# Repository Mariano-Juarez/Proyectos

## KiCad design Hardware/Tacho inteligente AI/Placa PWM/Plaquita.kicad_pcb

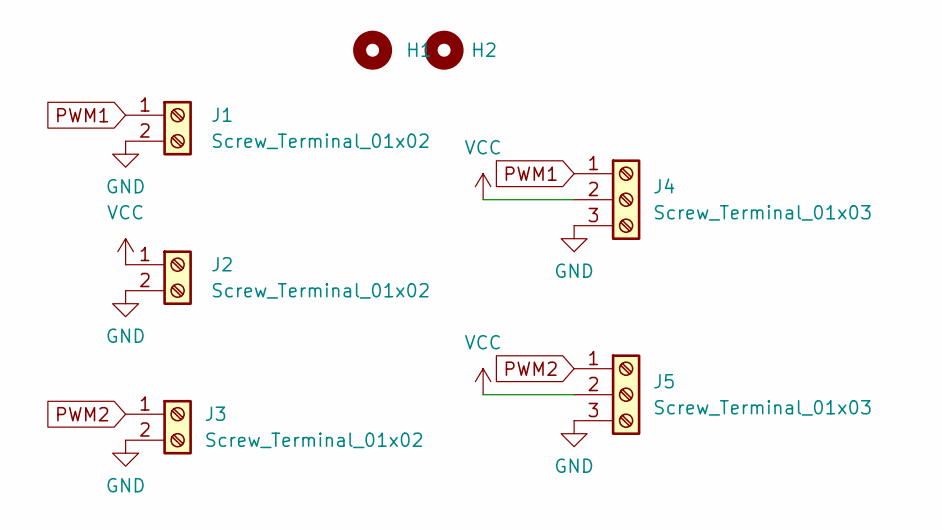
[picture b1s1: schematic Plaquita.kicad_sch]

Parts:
H1, H2: Mounting_Hole; MountingHole_3.5mm
J1, J2, J3: Screw_Terminal_01x02; TerminalBlock_Altech_AK300-2_P5.00mm
J4, J5: Screw_Terminal_01x03; TerminalBlock_Altech_AK300-3_P5.00mm

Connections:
GND: J1.2, J2.2, J3.2, J4.3, J5.3
PWM1: J1.1, J4.1
PWM2: J3.1, J5.1
VCC: J2.1, J4.2, J5.2

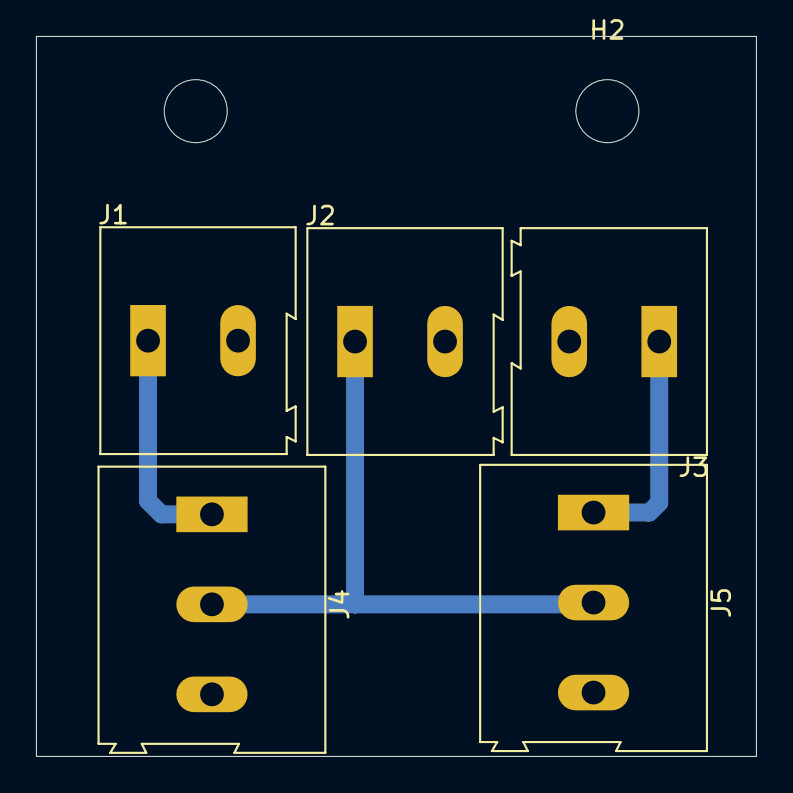
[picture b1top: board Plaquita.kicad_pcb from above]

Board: 2 copper layers, 40.0 x 40.0 mm, 7 parts (0 on the bottom side), 4 nets.

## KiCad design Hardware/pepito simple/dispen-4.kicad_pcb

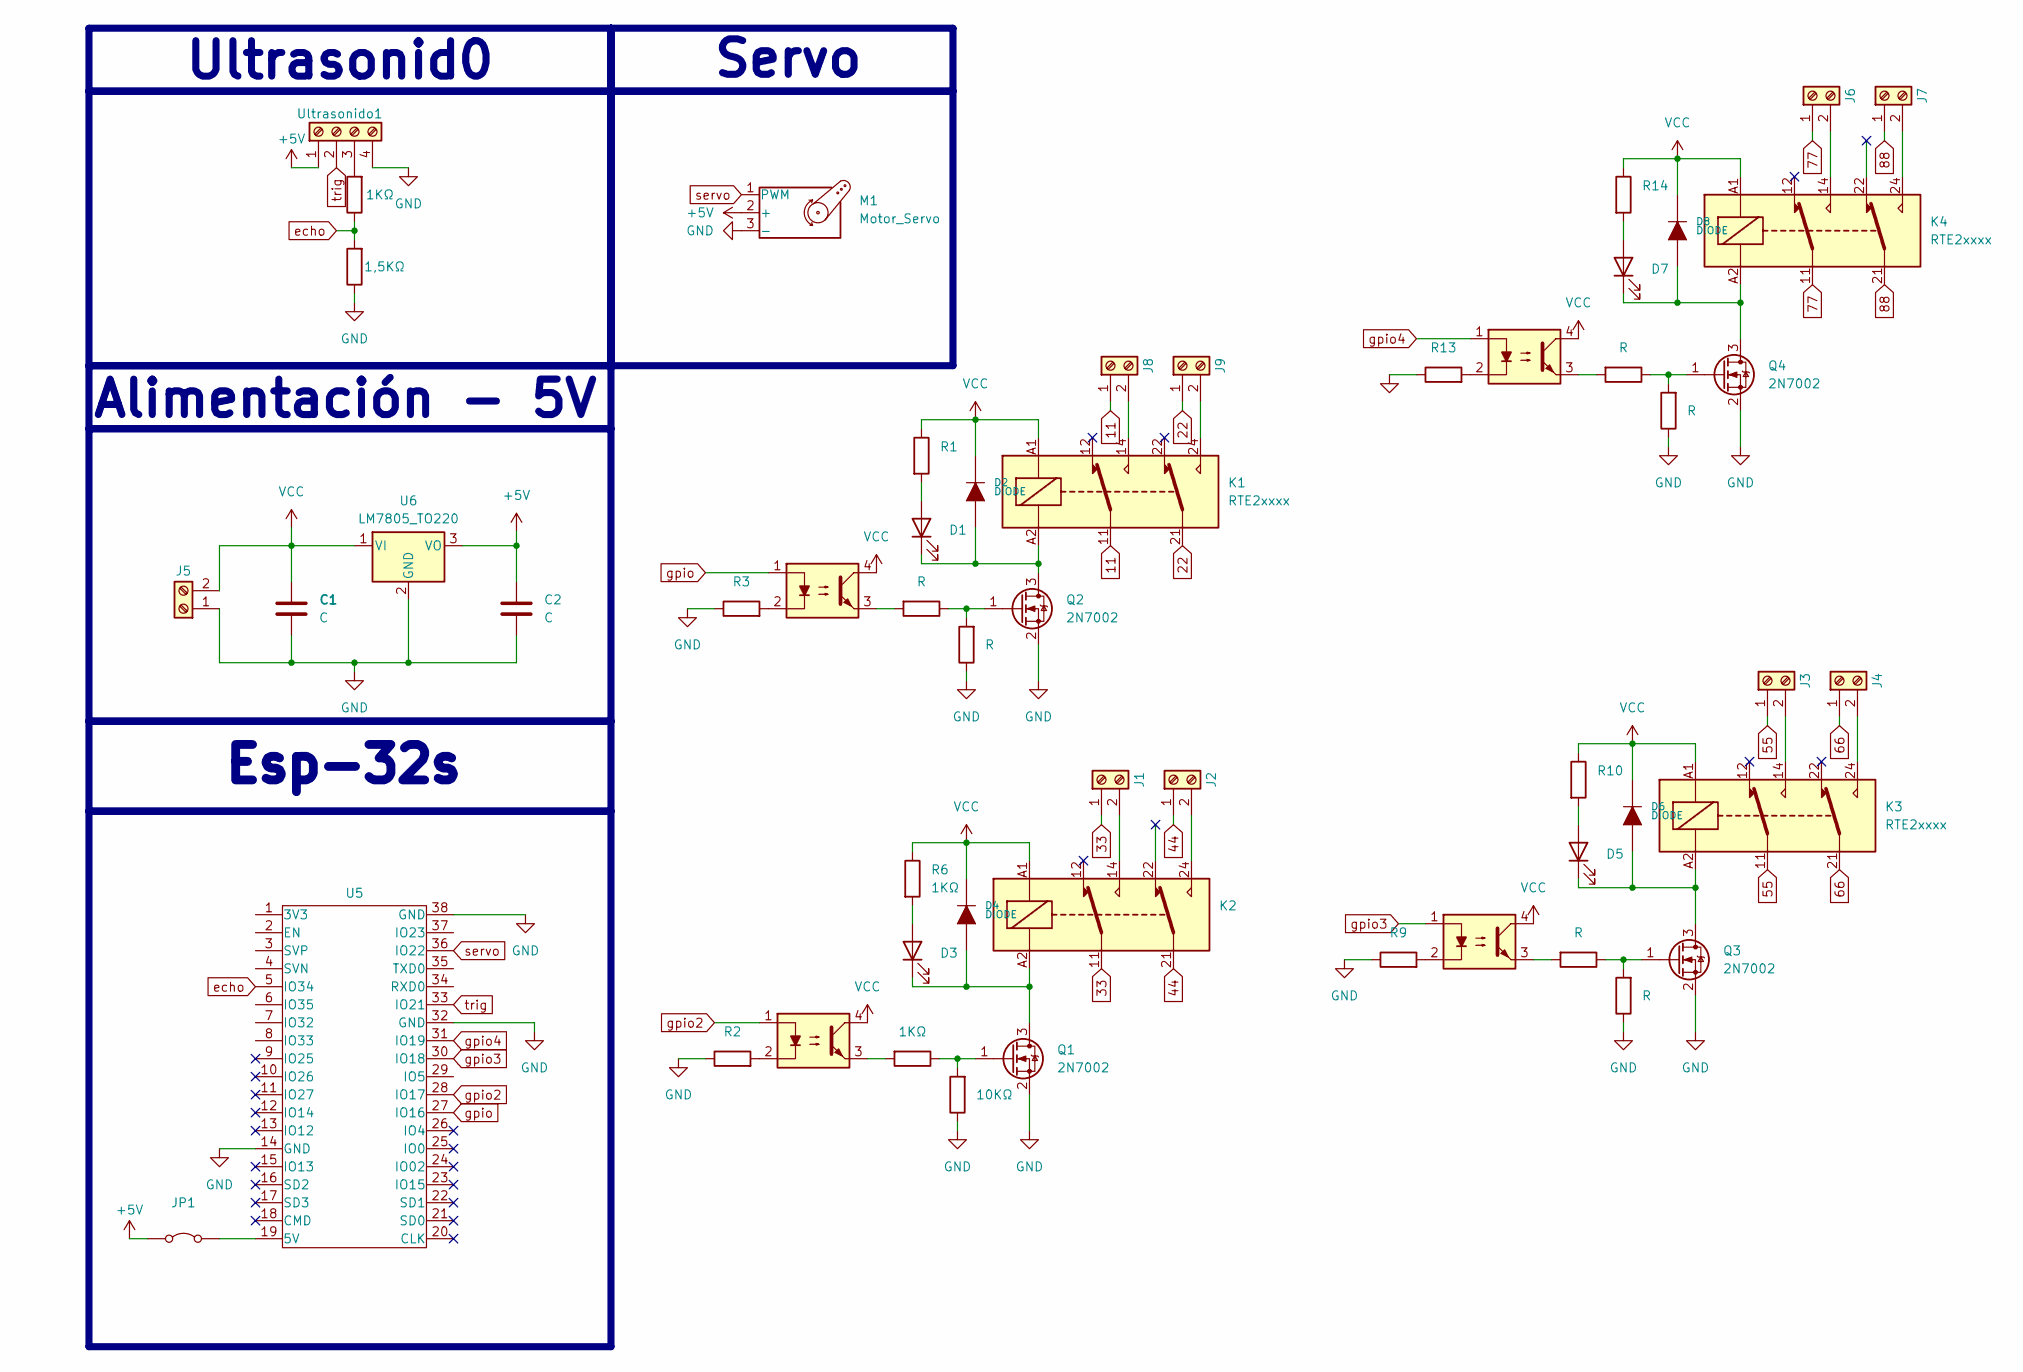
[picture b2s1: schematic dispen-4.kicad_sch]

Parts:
C1, C2: C; C_0805_2012Metric
D1, D3, D5, D7: LED; LED_0805_2012Metric
D2, D4, D6, D8: DIODE; D_SMA
J1, J2, J3, J4, J6, J7, J8, J9: Screw_Terminal_01x02; TerminalBlock_Altech_AK300-2_P5.00mm
J5: Screw_Terminal_01x02; TerminalBlock_Xinya_XY308-2.54-2P_1x02_P2.54mm_Horizontal
JP1: Jumper_2_Bridged; PinHeader_1x02_P2.54mm_Vertical
K1, K2, K3, K4: RTE2xxxx; Relay_DPDT_Schrack-RT2-FormC_RM5mm
M1: Motor_Servo; JST_XH_B3B-XH-A_1x03_P2.50mm_Vertical
Q1, Q2, Q3, Q4: 2N7002; SOT-23
R1, R3, R4, R5, R9, R10, R11, R12, R13, R14, R15, R16: R; R_0805_2012Metric
R2: 220Ω; R_0805_2012Metric
R6, R7, R17: 1KΩ; R_0805_2012Metric
R8: 10KΩ; R_0805_2012Metric
R18: 1,5KΩ; R_0805_2012Metric
U1, U2, U3, U4: PC817; DIP762W50P254L650H455Q4B
U5: ESP32_DEVKITC; ESP32S
U6: LM7805_TO220; TO-220-3_Vertical
Ultrasonido1: Screw_Terminal_01x04; JST_XH_B4B-XH-A_1x04_P2.50mm_Vertical

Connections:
11: J8.1, K1.11
22: J9.1, K1.21
33: J1.1, K2.11
44: J2.1, K2.21
55: J3.1, K3.11
66: J4.1, K3.21
77: J6.1, K4.11
88: J7.1, K4.21
+5V: C2.1, JP1.1 (A), M1.2 (+), U6.3 (VO), Ultrasonido1.1
GND: C1.2, C2.2, J5.1, M1.3 (-), Q1.2 (S), Q2.2 (S), Q3.2 (S), Q4.2 (S), R2.1, R3.1, R4.1, R8.1, R9.1, R12.1, R13.1, R16.1, R18.1, U5.14 (GND), U5.32 (GND), U5.38 (GND), U6.2 (GND), Ultrasonido1.4
unnamed: D1.2 (A), R1.2
unnamed: D1.1 (K), D2.1 (A), K1.A2, Q2.3 (D)
unnamed: D3.2 (A), R6.2
unnamed: D3.1 (K), D4.1 (A), K2.A2, Q1.3 (D)
unnamed: D5.2 (A), R10.2
unnamed: D5.1 (K), D6.1 (A), K3.A2, Q3.3 (D)
unnamed: D7.2 (A), R14.2
unnamed: D7.1 (K), D8.1 (A), K4.A2, Q4.3 (D)
unnamed: J1.2, K2.14
unnamed: J2.2, K2.24
unnamed: J3.2, K3.14
unnamed: J4.2, K3.24
unnamed: J6.2, K4.14
unnamed: J7.2, K4.24
unnamed: J8.2, K1.14
unnamed: J9.2, K1.24
unnamed: JP1.2 (B), U5.19 (5V)
unnamed: Q1.1 (G), R7.1, R8.2
unnamed: Q2.1 (G), R4.2, R5.1
unnamed: Q3.1 (G), R11.1, R12.2
unnamed: Q4.1 (G), R15.1, R16.2
unnamed: R2.2, U2.2
unnamed: R3.2, U1.2
unnamed: R5.2, U1.3
unnamed: R7.2, U2.3
unnamed: R9.2, U3.2
unnamed: R11.2, U3.3
unnamed: R13.2, U4.2
unnamed: R15.2, U4.3
unnamed: R17.2, Ultrasonido1.3
VCC: C1.1, D2.2 (K), D4.2 (K), D6.2 (K), D8.2 (K), J5.2, K1.A1, K2.A1, K3.A1, K4.A1, R1.1, R6.1, R10.1, R14.1, U1.4, U2.4, U3.4, U4.4, U6.1 (VI)
echo: R17.1, R18.2, U5.5 (IO34)
gpio: U1.1, U5.27 (IO16)
gpio2: U2.1, U5.28 (IO17)
gpio3: U3.1, U5.30 (IO18)
gpio4: U4.1, U5.31 (IO19)
servo: M1.1 (PWM), U5.36 (IO22)
trig: U5.33 (IO21), Ultrasonido1.2

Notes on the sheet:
Esp-32s
Alimentación - 5V
Ultrasonid0
Servo

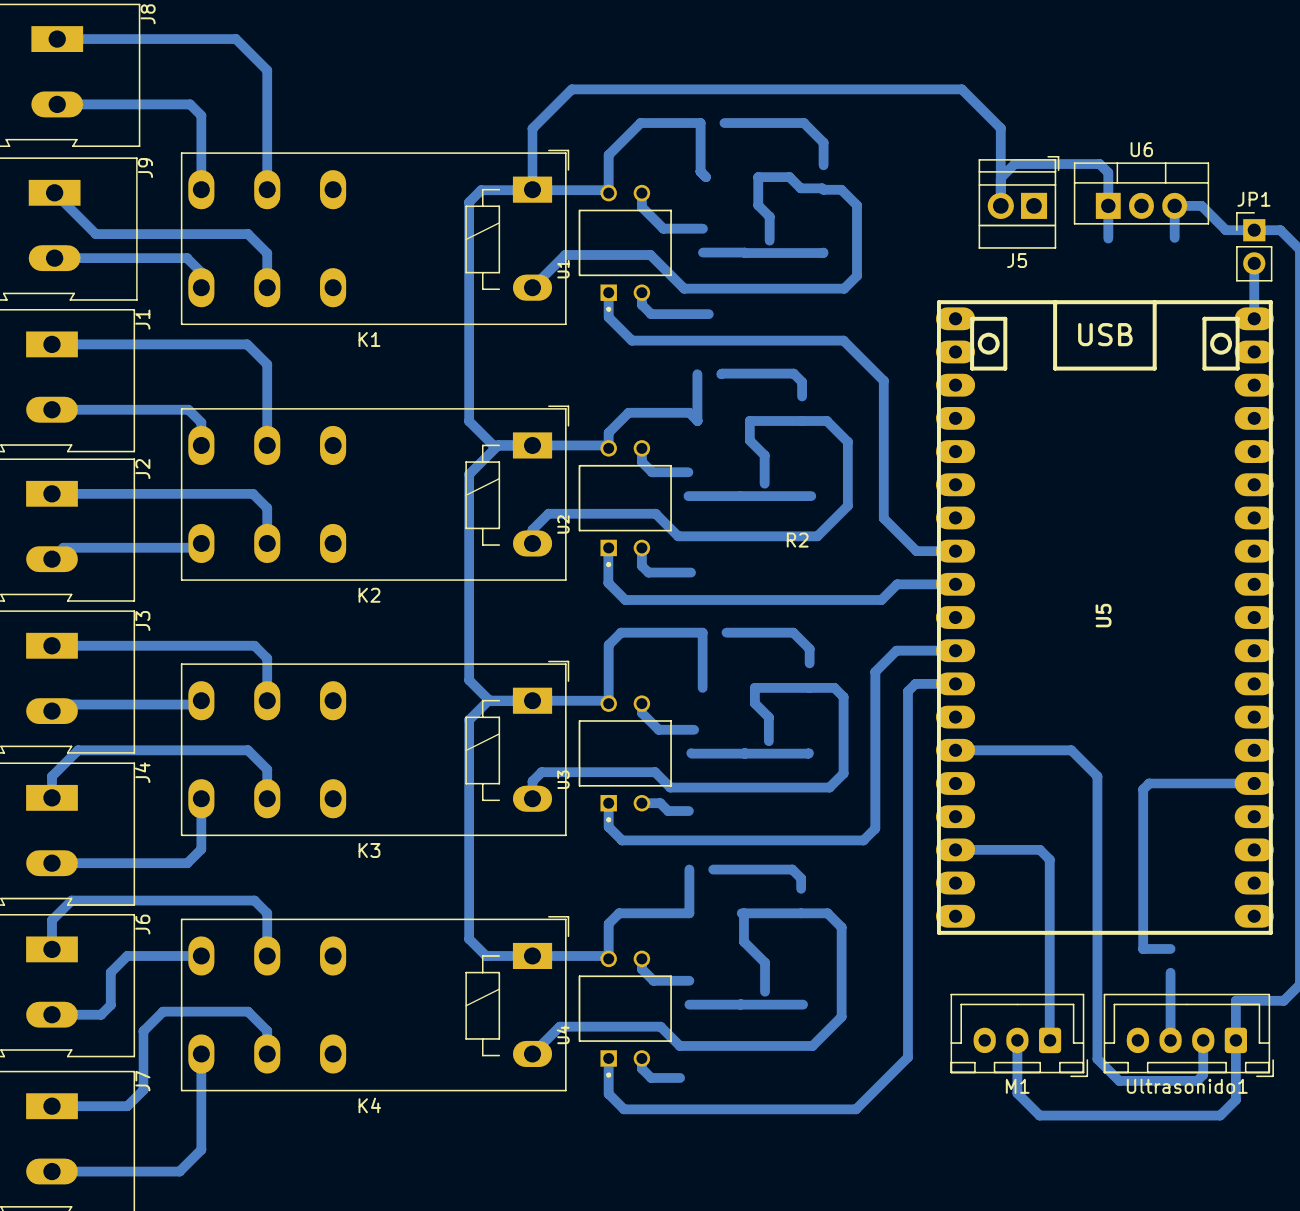
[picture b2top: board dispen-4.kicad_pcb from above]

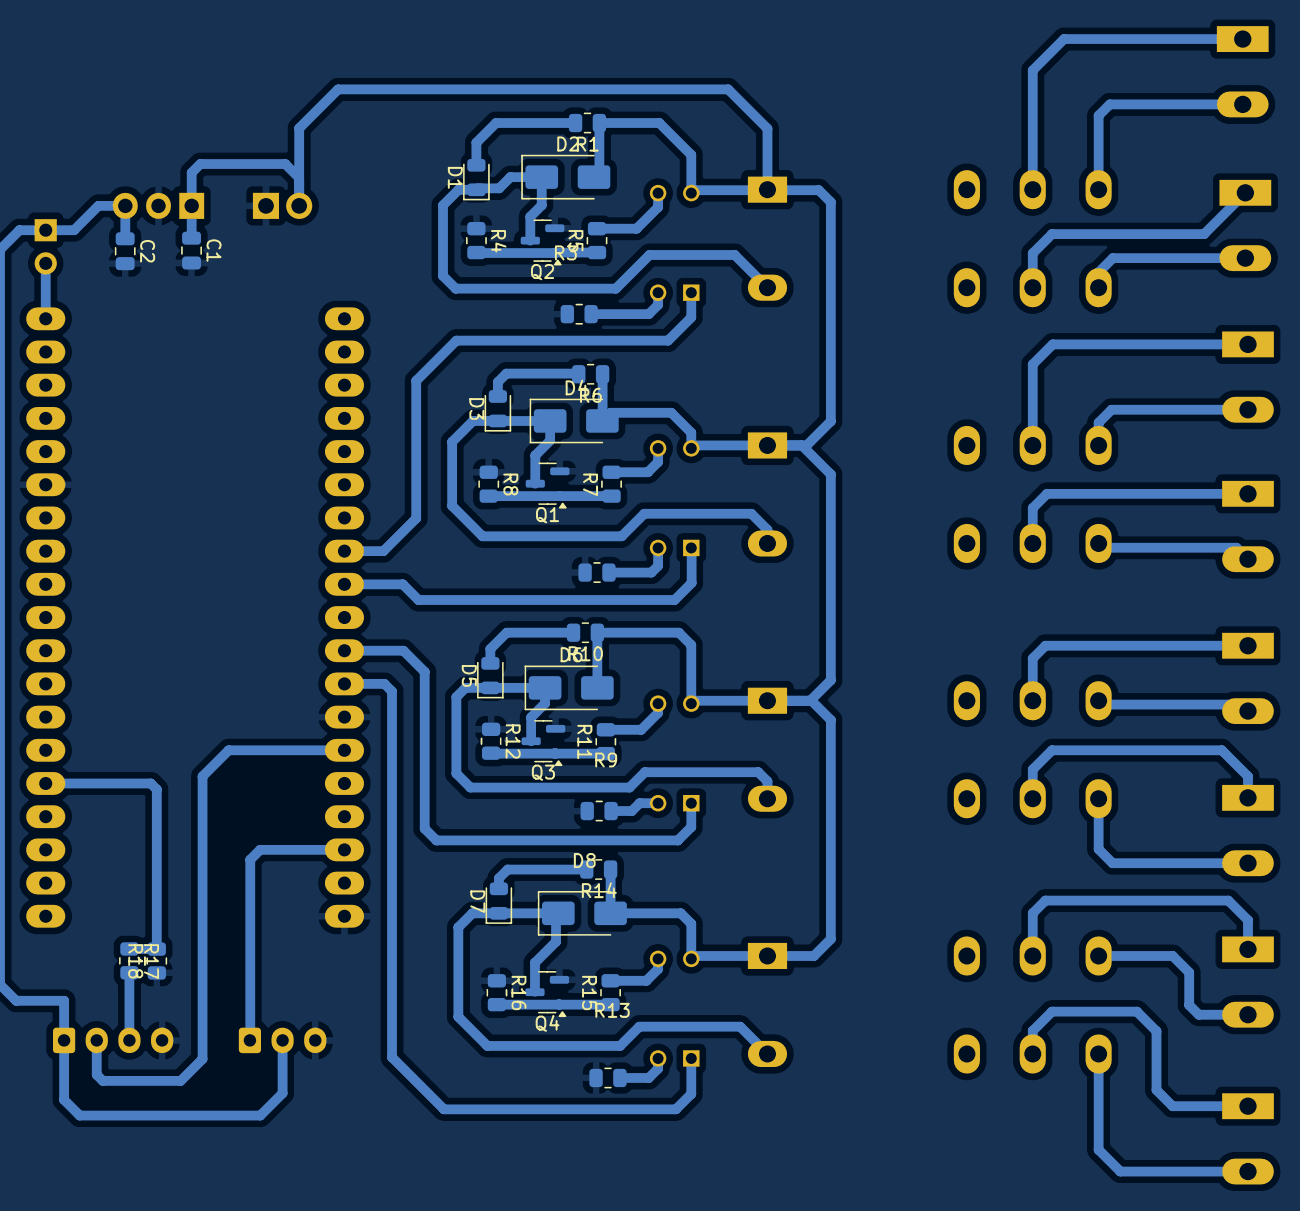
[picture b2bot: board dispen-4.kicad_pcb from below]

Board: 2 copper layers, 54 parts (32 on the bottom side), 48 nets.

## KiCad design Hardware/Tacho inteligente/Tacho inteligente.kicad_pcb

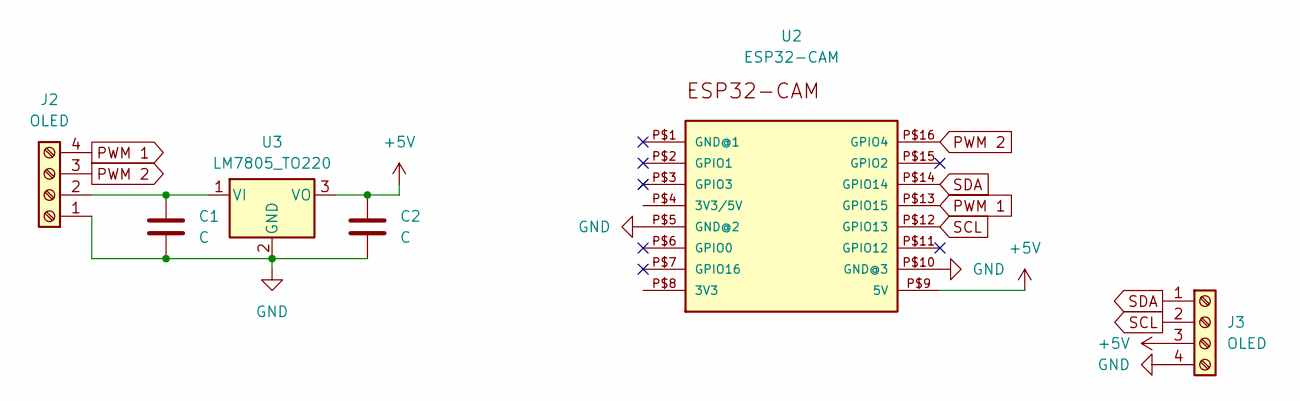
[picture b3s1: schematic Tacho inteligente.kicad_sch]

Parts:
C1, C2: C; C_0805_2012Metric
J2, J3: OLED; TerminalBlock_MaiXu_MX126-5.0-04P_1x04_P5.00mm
U2: ESP32-CAM
U3: LM7805_TO220; TO-263-3_TabPin2

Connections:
+5V: C2.1, J3.3, U2.P$9 (5V), U3.3 (VO)
GND: C1.2, C2.2, J2.1, J3.4, U2.P$5 (GND@2), U2.P$10 (GND@3), U3.2 (GND)
unnamed: C1.1, J2.2, U3.1 (VI)
PWM 1: J2.4, U2.P$13 (GPIO15)
PWM 2: J2.3, U2.P$16 (GPIO4)
SCL: J3.2, U2.P$12 (GPIO13)
SDA: J3.1, U2.P$14 (GPIO14)

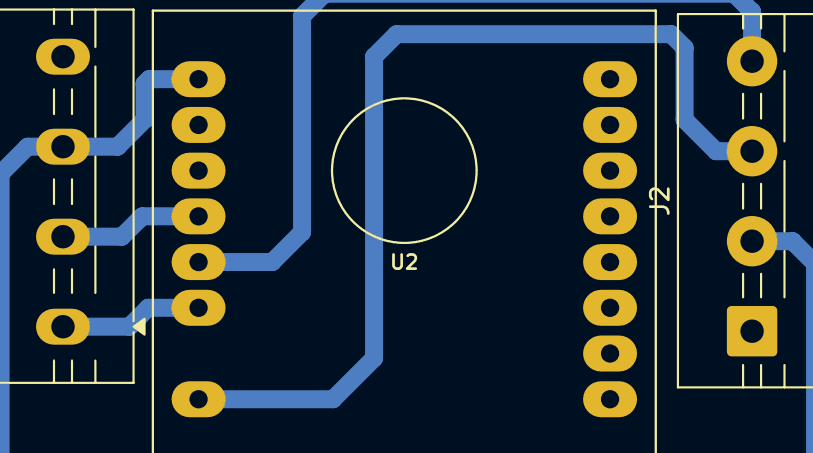
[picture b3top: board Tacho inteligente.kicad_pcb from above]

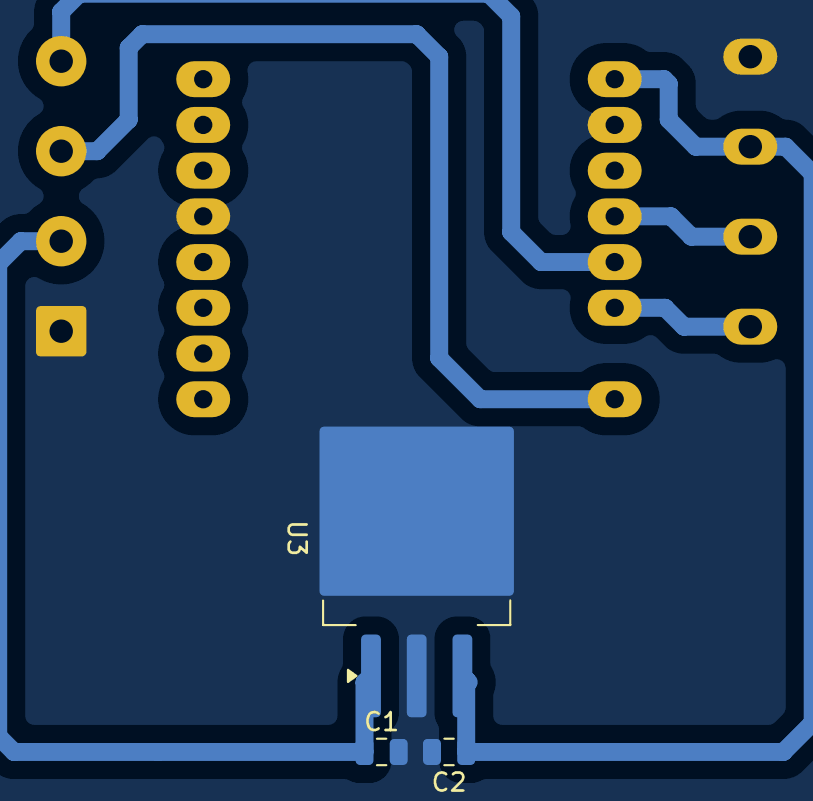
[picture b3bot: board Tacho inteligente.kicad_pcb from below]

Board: 2 copper layers, 6 parts (3 on the bottom side), 7 nets.

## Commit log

2025-06-02 Mi primer commit
2025-06-11 Tercer commit
2025-06-23 Cuarto commit
2025-06-25 quinto commit
2025-08-11 sexto commit
2025-09-05 7mo commit
2025-09-05 octavo commit
2025-11-28 decioprimer commit
2025-11-28 decimosegundo commit
2025-11-28 decimotercer commit
2025-11-28 decimocuarto commit
2025-11-28 decimo quinto commit
